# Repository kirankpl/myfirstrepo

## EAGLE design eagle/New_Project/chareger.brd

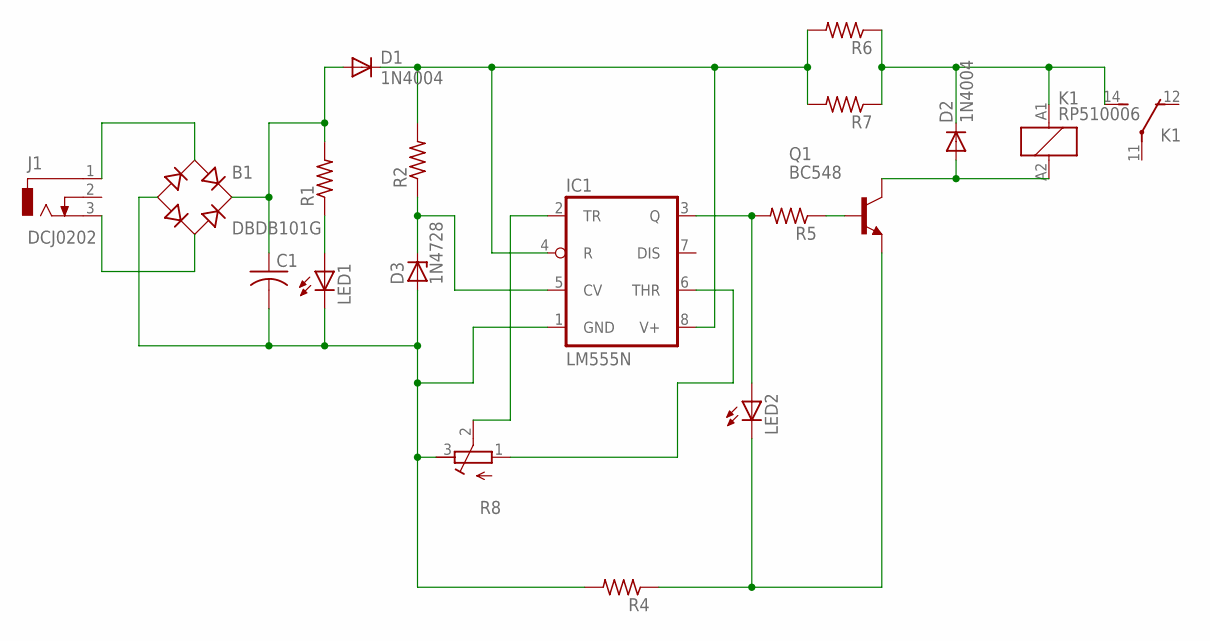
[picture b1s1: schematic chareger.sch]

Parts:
B1: DBDB101G; DB
C1: C-US025-050X050; C025-050X050
D1, D2: 1N4004; DO41-10
D3: 1N4728; DO41Z10
IC1: LM555N; DIL08-ROUND
J1: DCJ0202
K1: RP510006; RP51
LED1, LED2: LEDB152; Q62902-B152
Q1: BC548; TO92-EBC
R1, R2, R4, R5, R6, R7: R-US_0204/5; 0204/5
R8: R-TRIMM74X; RTRIM74X

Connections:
GND: B1.-, C1.2, D3.A, IC1.1 (GND), LED1.K (C), R4.2, R8.3 (E)
unnamed: B1.AC1, J1.1
unnamed: B1.AC2, J1.3
unnamed: B1.+, C1.1, D1.A, R1.2
unnamed: D1.C, IC1.4 (R), IC1.8 (V+), R2.2, R6.2, R7.2
unnamed: D3.C, IC1.5 (CV), R2.1
unnamed: IC1.2 (TR), R8.2 (S)
unnamed: IC1.6 (THR), R8.1 (A)
unnamed: Q1.B, R5.1
unnamed: IC1.3 (Q), LED2.A, R5.2
unnamed: LED2.K (C), Q1.E, R4.1
unnamed: D2.A, K1.A2 (2), Q1.C
unnamed: LED1.A, R1.1
unnamed: D2.C, K1.14 (S), K1.A1 (1), R6.1, R7.1

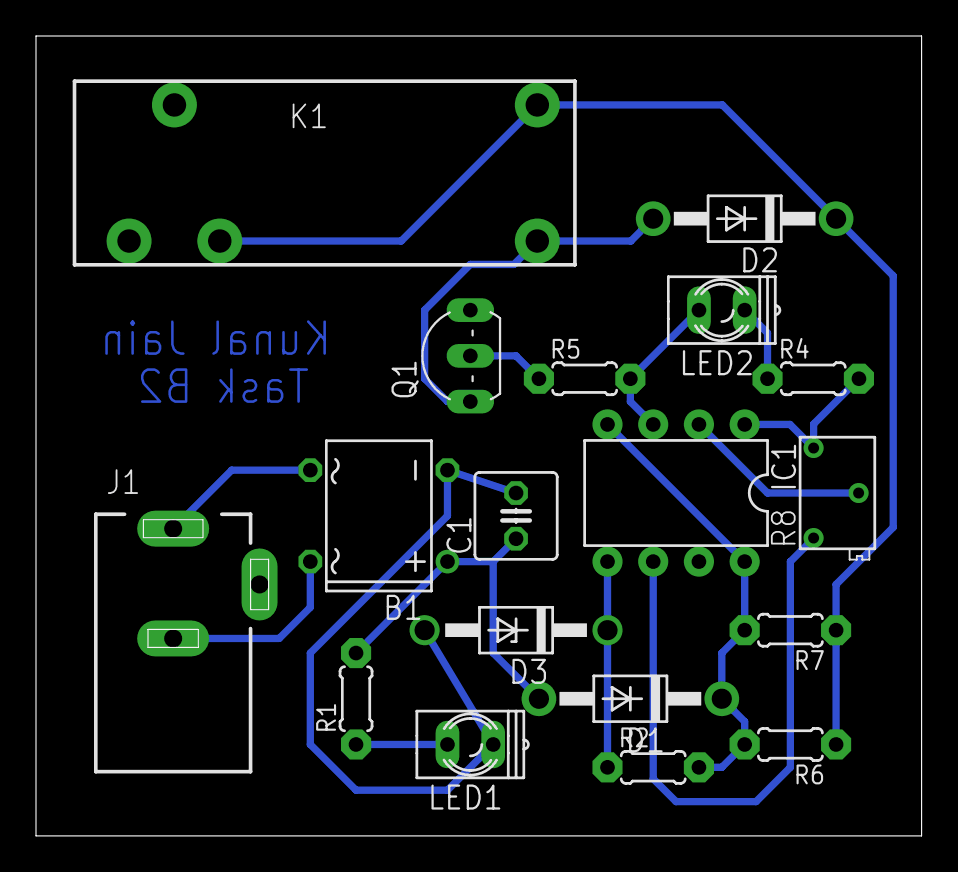
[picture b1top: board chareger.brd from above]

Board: 2 copper layers, 49.2 x 44.4 mm, 18 parts (0 on the bottom side), 14 nets.

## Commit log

2018-07-14 my first program
2018-07-14 Create gulga
